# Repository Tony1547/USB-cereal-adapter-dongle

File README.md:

# USB-cereal-adapter-dongle
USB-cereal-adapter-dongle
-----

I plan to make more PCB projects, so I'm making this to hopefully program them, also i hope to get better at soldering through this project 

This dongle uses the CH340C to communicate from USB to UART, and can be hung from a small keychain with the hole in the corner, also includes some personalization on the back of things that relate to me or the ysws

----

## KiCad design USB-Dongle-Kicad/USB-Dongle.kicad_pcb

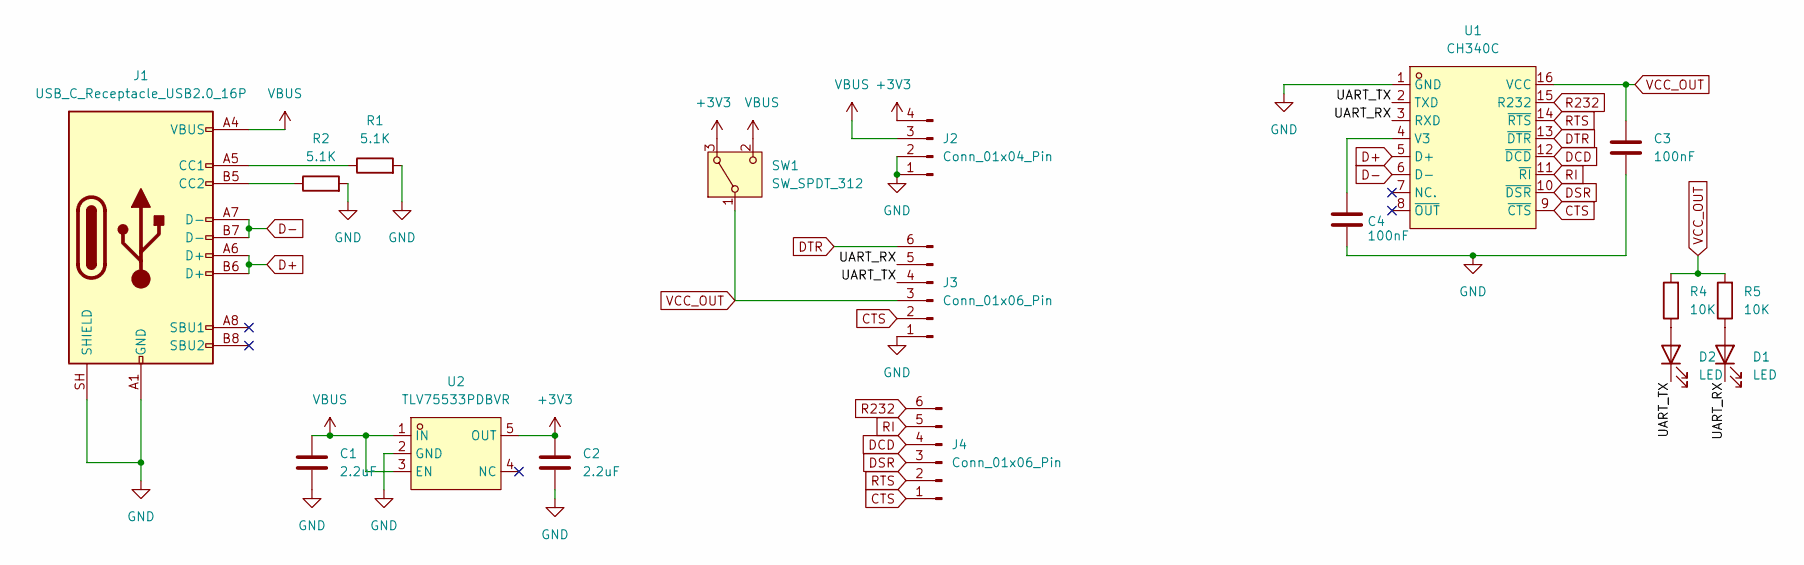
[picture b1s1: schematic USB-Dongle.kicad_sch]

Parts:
C1, C2: 2.2uF; C_0603_1608Metric_Pad1.08x0.95mm_HandSolder
C3, C4: 100nF; C_0603_1608Metric_Pad1.08x0.95mm_HandSolder
D1, D2: LED; LED_0402_1005Metric_Pad0.77x0.64mm_HandSolder
J1: USB_C_Receptacle_USB2.0_16P; USB_C_Receptacle_GCT_USB4105-xx-A_16P_TopMnt_Horizontal
J2: Conn_01x04_Pin; JST_EH_S4B-EH_1x04_P2.50mm_Horizontal
J3, J4: Conn_01x06_Pin; JST_EH_S6B-EH_1x06_P2.50mm_Horizontal
R1, R2: 5.1K; R_0805_2012Metric_Pad1.20x1.40mm_HandSolder
R4, R5: 10K; R_0805_2012Metric_Pad1.20x1.40mm_HandSolder
SW1: SW_SPDT_312; SW_SPDT_CK_JS102011SAQN
U1: CH340C; SOP-16_L10.0-W3.9-P1.27-LS6.0-BL; MPN CH340C; LCSC Part C84681
U2: TLV75533PDBVR; SOT-23-5_L3.0-W1.7-P0.95-LS2.8-BR; MPN TLV75533PDBVR; LCSC Part C404027

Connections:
+3V3: C2.1, J2.4, SW1.3 (A), U2.5 (OUT)
/UART_RX: D1.1 (K), J3.5, U1.3 (RXD)
/UART_TX: D2.1 (K), J3.4, U1.2 (TXD)
CTS: J3.2, J4.1, U1.9 (~CTS)
D+: J1.A6 (D+), J1.B6 (D+), U1.5 (D+)
D-: J1.A7 (D-), J1.B7 (D-), U1.6 (D-)
DCD: J4.4, U1.12 (~DCD)
DSR: J4.3, U1.10 (~DSR)
DTR: J3.6, U1.13 (~DTR)
GND: C1.2, C2.2, C3.1, C4.1, J1.A1 (GND), J1.A12 (GND), J1.B1 (GND), J1.B12 (GND), J1.SH (SHIELD), J2.1, J2.2, J3.1, R1.2, R2.2, U1.1 (GND), U2.2 (GND)
unnamed: D1.2 (A), R5.1
unnamed: D2.2 (A), R4.1
unnamed: J1.A5 (CC1), R1.1
unnamed: J1.B5 (CC2), R2.1
unnamed: C4.2, U1.4 (V3)
R232: J4.6, U1.15 (R232)
RI: J4.5, U1.11 (~RI)
RTS: J4.2, U1.14 (~RTS)
VBUS: C1.1, J1.A4 (VBUS), J1.A9 (VBUS), J1.B4 (VBUS), J1.B9 (VBUS), J2.3, SW1.2 (C), U2.1 (IN), U2.3 (EN)
VCC_OUT: C3.2, J3.3, R4.2, R5.2, SW1.1 (B), U1.16 (VCC)

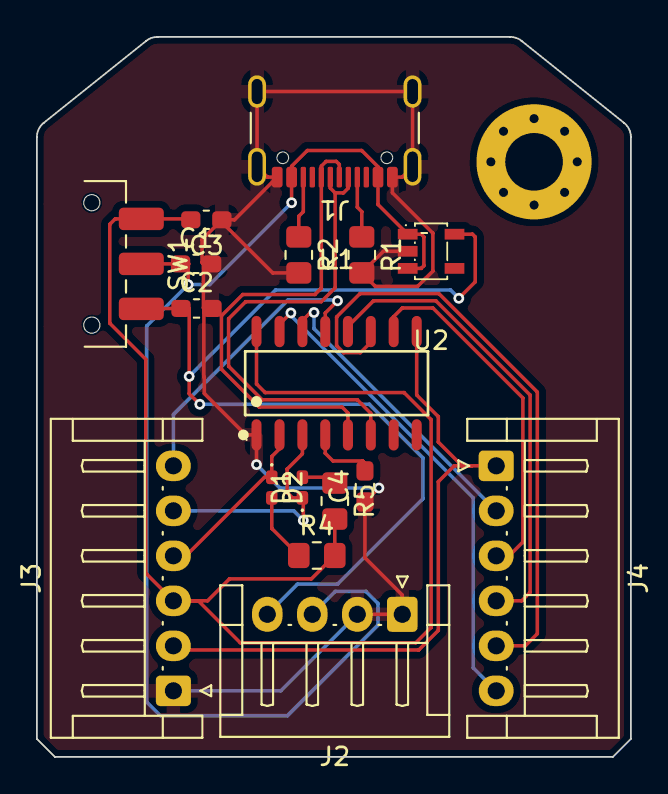
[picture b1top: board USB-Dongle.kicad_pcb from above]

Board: 2 copper layers, 33.0 x 40.0 mm, 17 parts (0 on the bottom side), 20 nets.

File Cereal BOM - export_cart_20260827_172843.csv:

Index,LCSC#,MPN,Manufacturer,Package,Customer #,Description,RoHS,Quantity,MOQ,Multiple,Unit Price($),Extended Price($),Product Link
1,C20089287,S6B-EH,JST,"Through Hole,P=2.5mm",,Connector Header 6 position 2.5mm Pitch 3A Right Angle -25℃~+85℃,yes,2,1,1,0.1963,0.39,https://www.lcsc.com/product-detail/C20089287.html
2,C27834,0805W8F5101T5E,UNI-ROYAL,805,,5.1kΩ ±1% 125mW 0805 Thick Film Resistor,yes,100,100,100,0.0113,1.13,https://www.lcsc.com/product-detail/C27834.html
3,C2907219,FRC0805F1002TS,FOJAN,805,,10kΩ ±1% 125mW 0805 Thick Film Resistor,yes,100,100,100,0.0035,0.35,https://www.lcsc.com/product-detail/C2907219.html
4,C84681,CH340C,WCH,SOP-16,,Transceiver 2Mbps USB 2.0 SOP-16 Interface Controllers ,yes,1,1,1,0.5879,0.59,https://www.lcsc.com/product-detail/C84681.html
5,C404027,TLV75533PDBVR,TI,SOT-23-5,,"3.3V Positive Fixed SOT-23-5 Voltage Regulators - Linear, Low Drop Out (LDO) Regulators RoHS",yes,5,5,5,0.1636,0.82,https://www.lcsc.com/product-detail/C404027.html
6,C23630,CL10A225KO8NNNC,Samsung Electro-Mechanics,603,,2.2uF ±10% 16V Ceramic Capacitor X5R 0603,yes,50,50,50,0.0196,0.98,https://www.lcsc.com/product-detail/C23630.html
7,C6119867,CGA0603X7R104K500JT,HRE,603,,100nF ±10% 50V Ceramic Capacitor X7R 0603,yes,100,100,100,0.0066,0.66,https://www.lcsc.com/product-detail/C6119867.html
8,C963206,MK-12C02-G020,G-Switch,"SMD,6.6x1.4mm",,"Slide Switch SPDT 1A @ 6V Surface Mount, Right Angle Rectangular Columnar 6.6mm",yes,5,5,5,0.1245,0.62,https://www.lcsc.com/product-detail/C963206.html
9,C22355736,XL-1005UBC,XINGLIGHT,402,,Blue 465nm LED Indication - Discrete 3.3V 0402,yes,50,50,50,0.008,0.4,https://www.lcsc.com/product-detail/C22355736.html
10,C165948,TYPE-C-31-M-12,Korean Hroparts Elec,SMD,,USB-C (USB TYPE-C) Receptacle Connector 16 Position Surface Mount,yes,5,5,5,0.1716,0.86,https://www.lcsc.com/product-detail/C165948.html
,,,,,,,,,,,,6.8,
,,,,,,,,,,,,$18.75 + shipping,
,,,,,,,,,,,,$10.18 for PCB,
